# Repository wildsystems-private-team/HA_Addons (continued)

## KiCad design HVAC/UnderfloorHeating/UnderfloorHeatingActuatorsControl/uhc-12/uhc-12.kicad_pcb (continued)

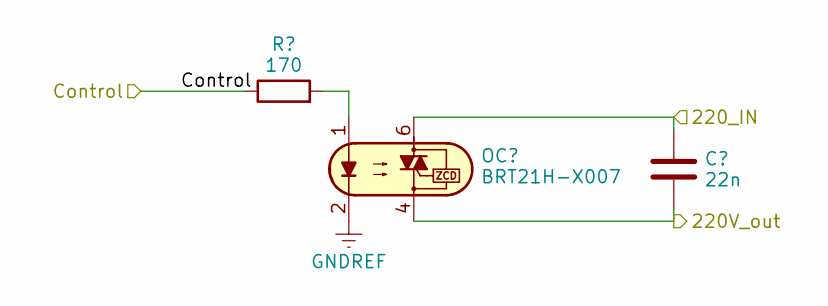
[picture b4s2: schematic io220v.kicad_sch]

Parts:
C2: 22n; C_0805_2012Metric
OC1: BRT21H-X007; SMDIP-6_W9.53mm
R1: 170; R_0805_2012Metric_Pad1.20x1.40mm_HandSolder

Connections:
/GPIO32: R1.1; also elsewhere on the board
/IO_220V/220V_out: C2.2, OC1.4; also elsewhere on the board
/L: C2.1, OC1.6; also elsewhere on the board
GNDREF: OC1.2; also elsewhere on the board
unnamed: OC1.1, R1.2

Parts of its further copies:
C3, C4, C5, C6, C7, C8, C9, C10, C11, C12, C13: 22n; C_0805_2012Metric
OC2, OC3, OC4, OC5, OC6, OC7, OC8, OC9, OC10, OC11, OC12: BRT21H-X007; SMDIP-6_W9.53mm
R2, R3, R4, R5, R6, R7, R8, R9, R10, R11, R12: 170; R_0805_2012Metric_Pad1.20x1.40mm_HandSolder

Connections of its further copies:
/GPIO16: R12.1; also elsewhere on the board
/GPIO17: R11.1; also elsewhere on the board
/GPIO18: R10.1; also elsewhere on the board
/GPIO19: R9.1; also elsewhere on the board
/GPIO21: R8.1; also elsewhere on the board
/GPIO22: R7.1; also elsewhere on the board
/GPIO23: R6.1; also elsewhere on the board
/GPIO25: R3.1; also elsewhere on the board
/GPIO26: R4.1; also elsewhere on the board
/GPIO27: R5.1; also elsewhere on the board
/GPIO33: R2.1; also elsewhere on the board
/IO_220V1/220V_out: C3.2, OC2.4; also elsewhere on the board
/IO_220V2/220V_out: C4.2, OC3.4; also elsewhere on the board
/IO_220V3/220V_out: C5.2, OC4.4; also elsewhere on the board
/IO_220V4/220V_out: C6.2, OC5.4; also elsewhere on the board
/IO_220V5/220V_out: C7.2, OC6.4; also elsewhere on the board
/IO_220V6/220V_out: C13.2, OC12.4; also elsewhere on the board
/IO_220V7/220V_out: C11.2, OC10.4; also elsewhere on the board
/IO_220V8/220V_out: C10.2, OC9.4; also elsewhere on the board
/IO_220V9/220V_out: C9.2, OC8.4; also elsewhere on the board
/IO_220V10/220V_out: C8.2, OC7.4; also elsewhere on the board
/IO_220V11/220V_out: C12.2, OC11.4; also elsewhere on the board
/L: C3.1, C4.1, C5.1, C6.1, C7.1, C8.1, C9.1, C10.1, C11.1, C12.1, C13.1, OC2.6, OC3.6, OC4.6, OC5.6, OC6.6, OC7.6, OC8.6, OC9.6, OC10.6, OC11.6, OC12.6; also elsewhere on the board
GNDREF: OC2.2, OC3.2, OC4.2, OC5.2, OC6.2, OC7.2, OC8.2, OC9.2, OC10.2, OC11.2, OC12.2; also elsewhere on the board
unnamed: OC2.1, R2.2
unnamed: OC3.1, R3.2
unnamed: OC4.1, R4.2
unnamed: OC5.1, R5.2
unnamed: OC6.1, R6.2
unnamed: OC7.1, R7.2
unnamed: OC8.1, R8.2
unnamed: OC9.1, R9.2
unnamed: OC10.1, R10.2
unnamed: OC11.1, R11.2
unnamed: OC12.1, R12.2

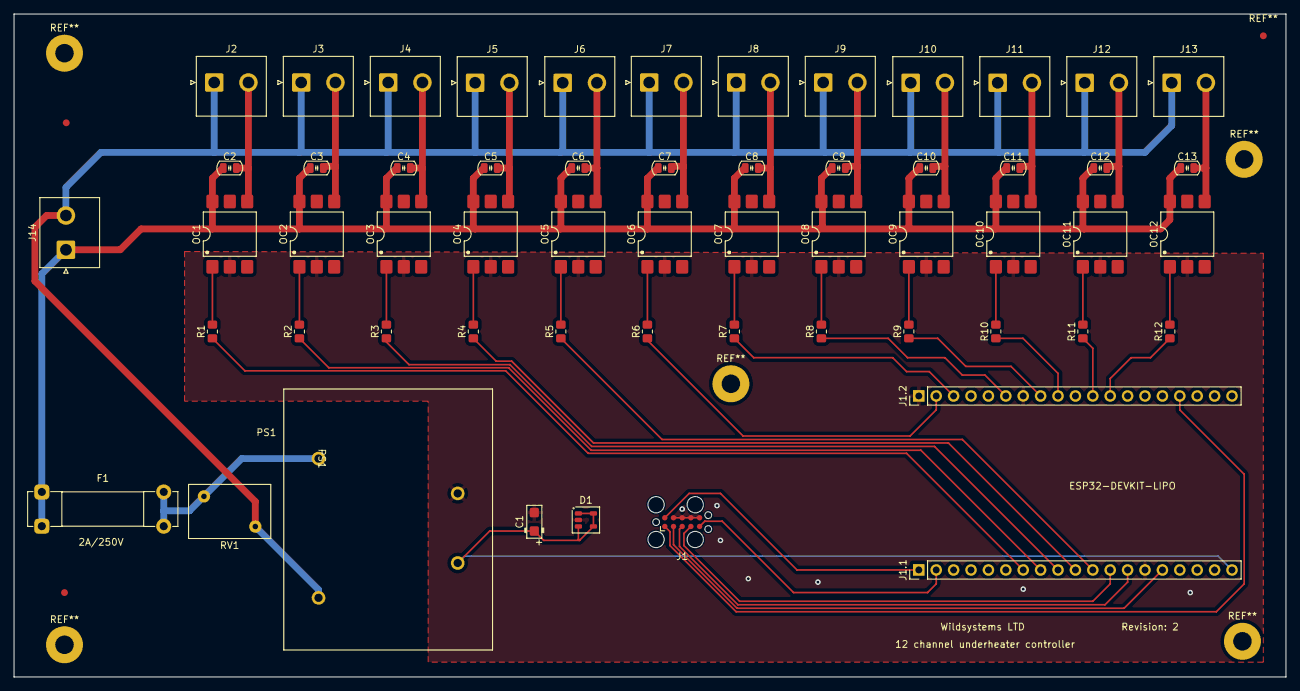
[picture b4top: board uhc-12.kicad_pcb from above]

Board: 2 copper layers, 185.7 x 96.8 mm, 57 parts (0 on the bottom side), 47 nets.

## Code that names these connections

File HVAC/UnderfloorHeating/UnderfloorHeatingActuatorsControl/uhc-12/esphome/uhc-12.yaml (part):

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  friendly_name: "Underfloor Controller"
  device_description: "This device is designed to control underfloor heating according to a preset temperature"
  log_level: DEBUG
  pwm_gpio_pin: GPIO15
  pwm_gpio_period: 20min

# PID parameters:
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  temp_sensor_12: temp_sensor_12

# Output pins for 
  output_1_pin: GPIO32
  output_2_pin: GPIO33
  output_3_pin: GPIO25
  output_4_pin: GPIO26
  output_5_pin: GPIO27
  output_6_pin: GPIO23
  output_7_pin: GPIO22
  output_8_pin: GPIO21
  output_9_pin: GPIO19
  output_10_pin: GPIO18
  output_11_pin: GPIO17
  output_12_pin: GPIO16

esphome:
  name: ${system_name}
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
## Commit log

2023-11-25 Reorganization
2023-11-25 esphome Modbus controller for ic100cx
2023-11-26 Added variables for NPT sensors
2023-11-29 addded ichill NTP sensors
2023-11-29 Rename dixell-ic200cx-interface to dixell-ic200cx-interface.yaml
2023-11-30 worspace config
2023-11-30 Added version with 4 outputs
2023-11-30 Case for the board
2023-12-01 Modified case
2023-12-03 esphome config added
2023-12-13 corrected typo in names
2023-12-13 DefinedRequirements. Closes #2
2023-12-13 added description of modus registers
2023-12-14 supplemented requirements
2024-02-21 24V 8 cahnnel underfloor heating controler addedd
2024-03-06 For review
2024-10-05 Folder reorganization
2024-10-05 Folder structure reorganization
2024-10-24 Ready for fabrication
